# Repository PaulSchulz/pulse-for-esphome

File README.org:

#+TITLE: Pulse for ESPHome
#+AUTHOR: Paul Schulz

* Contents :TOC:
- [[#introduction][Introduction]]
- [[#repository][Repository]]
- [[#software-and-utilities][Software and Utilities]]
- [[#hardware-development][Hardware Development]]
  - [[#kicad][Kicad]]
  - [[#m5stamps3-microcontroller-board][M5StampS3 Microcontroller Board]]
- [[#software-development-with-esphome][Software Development with ESPHome]]
- [[#construction][Construction]]
- [[#license][License]]
- [[#resources][Resources]]
- [[#acknowledgments-and-thankyous][Acknowledgments and Thankyous]]

* Introduction
This is an [[https://esphome.io][ESPHome]] project called *pulse-for-esphome*, based on the Home Assistant Glow
which was originally created in 2011. (For more background on this project see: [[https://glow-energy.io]])

The first version of this device (hardware and firmware) has been released and
is available as a kit or completed unit. As it is also open hardware, you can
also use these files to create your own device.

A presentation on the device (with more context) called "Catch the Flash:
Measuring household power usage" was given at the [[https://2026.everythingopen.au][Everything Open 2026]]
Conference in Canberra, Australia. Presentations are available [[docs/presentations][here]].

[[file:images/installed.jpg]]

* Repository
- GitHub: https://github.com/PaulSchulz/pulse-for-esphome

* Software and Utilities

* Hardware Development
** Kicad
Kicad has been used to create a printed circuit board (PCB) which is used to
mount the microcontroller and connector for the 'flash' sensor (photodiode)
and pulse LED (for monitoring).

See: [[kicad]]

#+ATTR_HTML: :width 300px
#+ATTR_ORG: :width 300px
[[file:images/pulse-for-esphome-pcb-front.png]]

#+ATTR_HTML: :width 300px
[[file:images/pulse-for-esphome-pcb-back.png]]

** M5StampS3 Microcontroller Board

The M5StampS3 is a microcontroller board, using the ESP32-S3 microcontroller
(MCU) which is a very capable processor for running ESPHome firmware. [[https://m5stack.com/][M5Stack]]
have mounted the processor, WiFi antenna, USB-C connector, Button and Status LED in a
very handy [[https://shop.m5stack.com/products/m5stamps3a-with-1-27-header-pin][inexpensive package]].

* Software Development with ESPHome
The firmware for this device uses [[https://esphome.io/][ESPHome]]

The YAML files can be found in the [[esphome]] directory.
 
* Construction
See: [[file:docs/construction.org][BOM and Hardware Assembly Notes]]

* License
This project is licensed under the MIT License. See the [[file:LICENSE][LICENSE]] file for details.

* Resources
 TBD

* Acknowledgments and Thankyous
The project would not have been possible without the help and assistance of the
following people and groups:

- Robert Hart and the Port Adelaide Enfield Council Library - IoT Experimenters Group
- Ewan Parsons, from V3G
- Klaas Schout, and the original Home Assistant Glow project ([[https://glow-energy.io]])

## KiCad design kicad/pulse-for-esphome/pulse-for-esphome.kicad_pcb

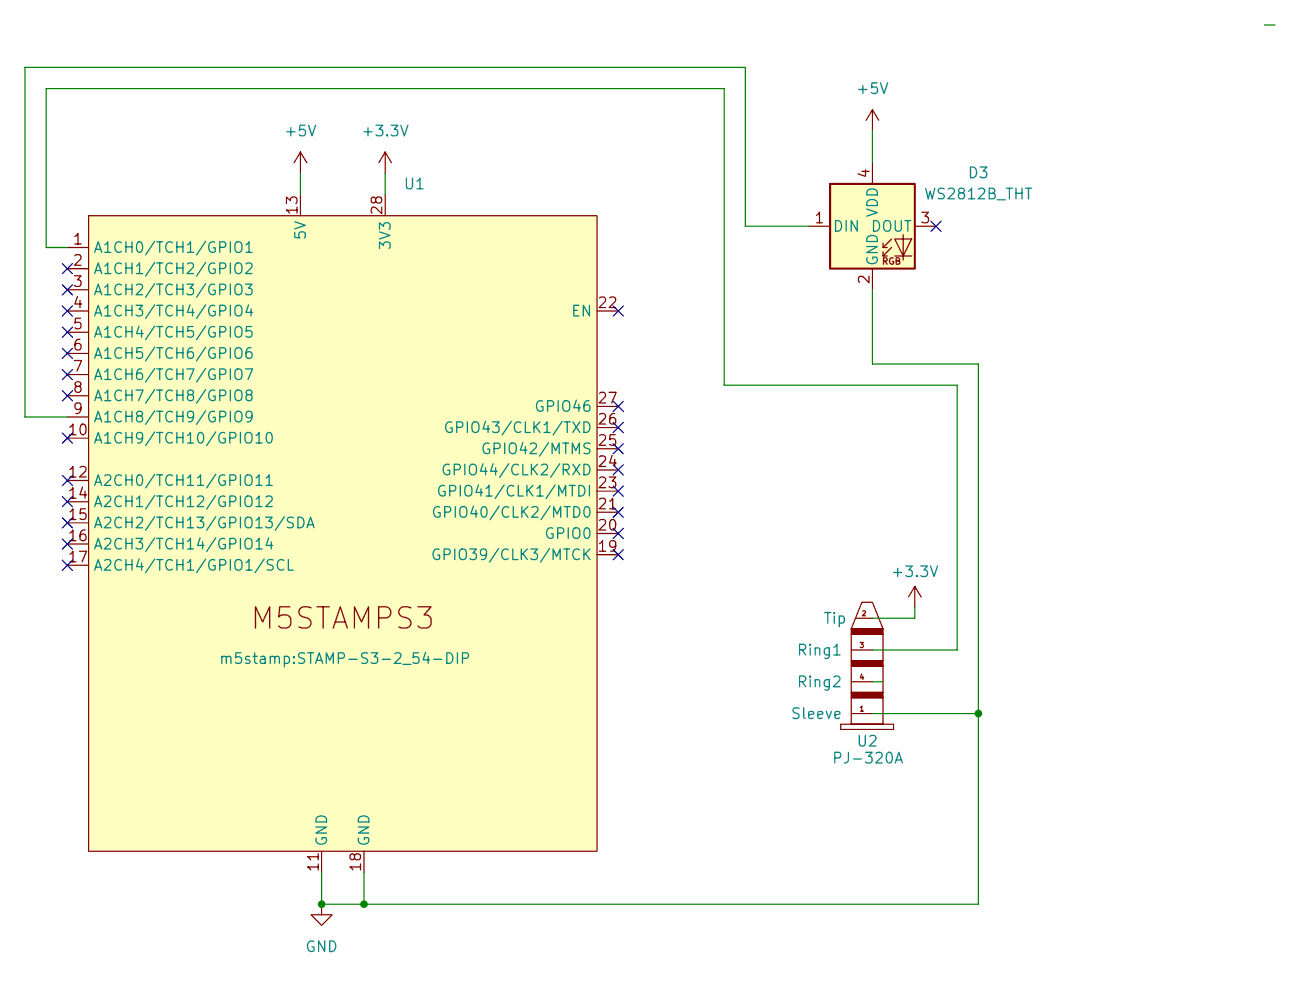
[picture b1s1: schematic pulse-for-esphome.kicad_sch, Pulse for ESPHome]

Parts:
D3: WS2812B_THT; LED_D5.0mm-4_RGB_Staggered_Pins
U1: STAMP-S3-2_54-DIP
U2: PJ-320A

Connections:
+3.3V: U1.28 (3V3), U2.2 (Tip)
+5V: D3.4 (VDD), U1.13 (5V)
GND: D3.2 (GND), U1.11 (GND), U1.18 (GND), U2.1 (Sleeve)
unnamed: D3.1 (DIN), U1.9 (A1CH8/TCH9/GPIO9)
unnamed: U1.1 (A1CH0/TCH1/GPIO1), U2.3 (Ring1)

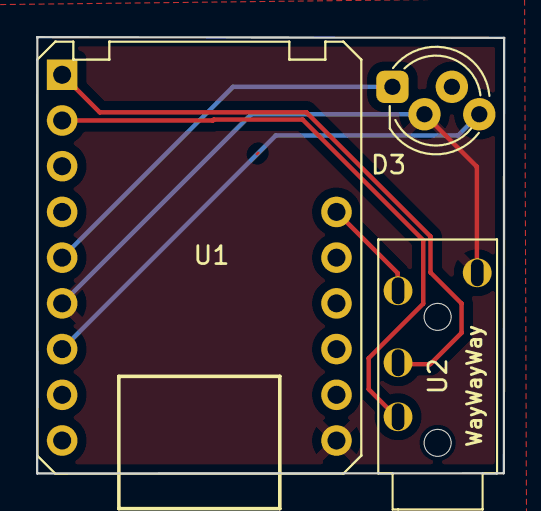
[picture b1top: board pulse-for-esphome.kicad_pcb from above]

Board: 2 copper layers, 25.9 x 24.2 mm, 3 parts (0 on the bottom side), 5 nets.

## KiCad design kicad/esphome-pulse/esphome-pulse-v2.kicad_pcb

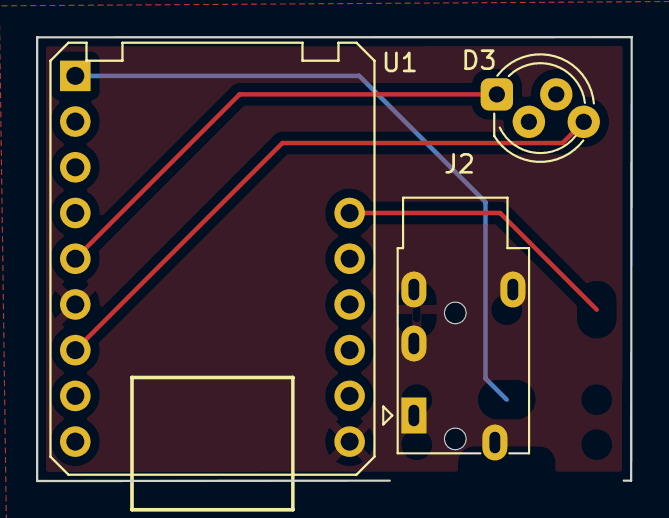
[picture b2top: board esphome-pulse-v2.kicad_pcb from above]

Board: 2 copper layers, 33.0 x 24.7 mm, 3 parts (0 on the bottom side), 5 nets.

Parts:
D3: WS2812B_THT; LED_D5.0mm-4_RGB_Staggered_Pins
J2: AudioJack2; Jack_3.5mm_PJ320E_Horizontal
U1: STAMP-S3-2_54-DIP

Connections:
+3.3V: J2.T, U1.28 (3V3)
+5V: D3.4 (VDD), U1.13 (5V)
GND: D3.2 (GND), U1.11 (GND), U1.18 (GND)
unnamed: D3.1 (DIN), U1.9 (A1CH8/TCH9/GPIO9)
unnamed: J2.S, U1.1 (A1CH0/TCH1/GPIO1)

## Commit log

2025-04-22 Initial commit of PCB design
2025-04-26 Sent to production
2025-05-09 Add second version of PCB with smaller barrel jack
2025-05-14 Remove older files and add README
2025-05-14 Update README with development notes
2025-05-14 Minor update to README
2025-05-14 Minor updates to README
2025-05-20 Update PCB and add images to README
2025-07-20 Added the pulse meter code
    This corrects the fact that this had not been added.
2025-07-21 kicad: Close board outline cut
    This error was raised in the Engineering Design Rule checks.
2025-08-01 docs: Add and fix some missing documentation
2025-08-01 esphome: Commit firmware changes
    - Use improv serial and bluetooth to provision wifi details.
    - Add 'factory reset' if user button held down for 4 seconds
    (with LED flash to confirm)
2025-08-01 images: Rename PCB images
2025-08-01 README: Minor edit to fix image name
2025-08-01 README: Update with picture of produced hardware
2025-08-01 images: Added installed image
2025-08-01 README: Adds front and backl images of PCB from Kicad
2025-08-05 images: Add new 'installed' image
2025-08-08 firmware: 1.0.1 - Adds missing configuration for pulse sensor
    While working with the original Home Assistant Glow, it was discovered that
    additional configuration was needed to stop double triggering when registering a
    pulse.
    This had not been added to the firmware for esphome-pulse.
2025-08-08 doc: Adds Installation Guide
2025-08-09 docs: Adds booklet pdf
2025-08-30 Rename from 'esphome-pulse' to 'pulse-for-esphome'
    This is a requirement for the "Made for ESPHome" certification.
    See: https://esphome.io/guides/made_for_esphome/
    More changes are required.
2025-08-30 doc: Add instructions for folding booklet
2025-08-30 doc: Minor edit to construction notes
2025-08-30 Remove 'secrets' file and associated settings
2025-08-30 doc: Remove references to 'secrets' file in README
    The 'secrets.yaml' file is no longer needed, or desired, for ESPHome devices,
    and so has been removed. Notes on how the 'secrets' file was previously
    configured in this project has been removed from the README file.
2025-08-30 docs: Add folding instructions for instruction booklet
2025-09-02 hardware: Migrate project name to pulse-for esphome
2025-09-02 firmware: Change LED component to fastled_clockless
    This change was done as the 'esp32_rmt_led_strip' was having problems with the
    newer version of ESPHome (and newer libraries). FastLED works with ESPHome
    versions to 2025.9.0-dev (including 2025.8.2)
    Also:
    - Moved the configs from 'common' into the main script (and removed the common dir.)
    - Added OTA updates from the webpage.
2025-09-02 docs: Updates README
2025-09-03 docs: Adds to construction notes
2025-09-03 docs: Adds images, and fixes naming
2025-09-03 docs: (minor) Fixes file renaming issue
2025-09-03 docs: (minor) Fixed up README
2025-09-03 docs: (minor) Updates README, and adds table of contents
2025-09-03 docs: (minor) Typo in README
2025-10-07 utils: Added python utility for logging pulse data
2025-10-14 utils: Initial comit pf utility to produce custom device file
2025-10-14 utils: Add Improv QRcode to access documentation
2025-10-14 docs: Updated README file
2025-10-14 docs: Fix typo in README
2025-10-14 pulse-fetch-data: Update log file format
    Added format version header.
    Format version: powershare 1.0.0
    - datetime_utc - including seconds
    - datetime_local - including seconds
    - total_watt_hours_in
    - total_watt_hours_out - currently 0, included for future bi-directional
2025-10-16 utils: Changed logging date format to be more universal
    Changed date format from %d/%m/%Y -> %Y-%m-%d
2026-01-29 doc: Add presentation slides from Open Everything 2026
2026-01-29 README: Update with presentation details
2026-01-29 README: Update with presentation details(2)
2026-02-09 firmware: Add 'for ESPHome' settings
    - Added project name and version, as required by 'for ESPHome' settings.
    - Added commented out mqtt section for reference.
    - Added set on reset timeout on API, to support sensors which are note connected
    to Home Assistant API (otherwise device will reboot if not accessed via API).
2026-02-09 firmware: Update firmware verson
2026-02-09 firmware: Merge YAML into single file (1.0.3)
    When using updates from internet can't use multiple file configurations.
2026-02-09 firmware: 1.0.5 Change import_full_config to false
    Also:
    - Removed '/' from name. Used exclusively for URLs
2026-02-11 firmware: 1.0.6 Add Wifi signal sensor
2026-02-16 firmware: 1.0.7 Adds internal temperature sensor
2026-03-27 firmware: pulse2-for-esphome 1.0.6 - Adds uptime sensor
